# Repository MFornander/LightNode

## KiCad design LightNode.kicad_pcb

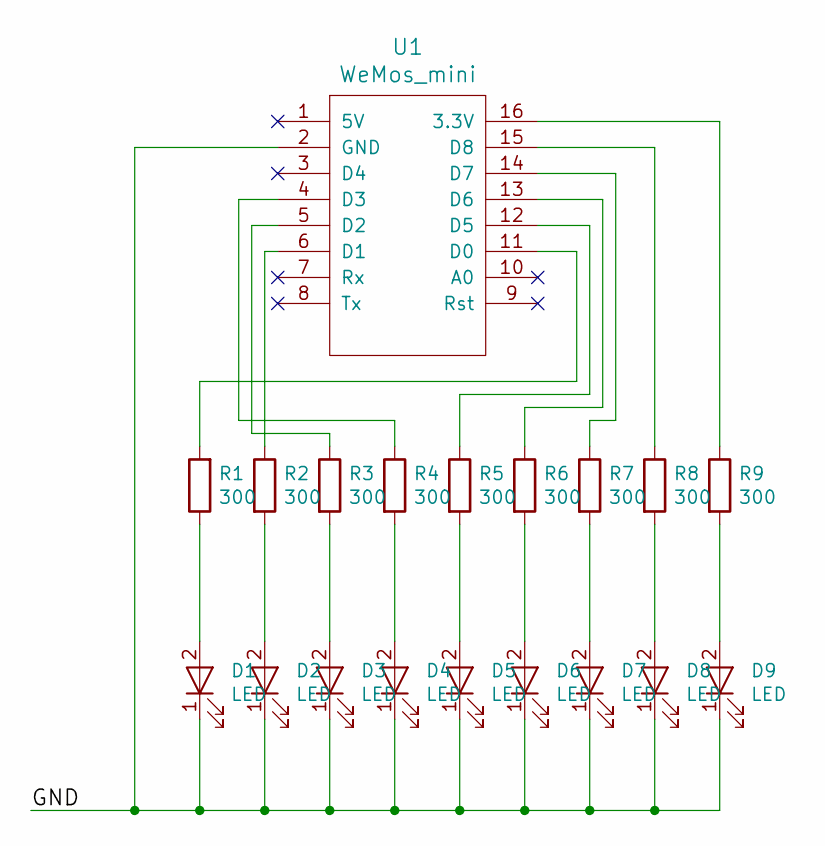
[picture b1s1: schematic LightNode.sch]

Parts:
D1, D2, D3, D4, D5, D6, D7, D8, D9: LED; LED_0805
R1, R2, R3, R4, R5, R6, R7, R8, R9: 300; R_0805
U1: WeMos_mini; D1_mini_board

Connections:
/GND: D1.1 (K), D2.1 (K), D3.1 (K), D4.1 (K), D5.1 (K), D6.1 (K), D7.1 (K), D8.1 (K), D9.1 (K), U1.2 (GND)
unnamed: D1.2 (A), R1.1
unnamed: D2.2 (A), R2.2
unnamed: D3.2 (A), R3.2
unnamed: D4.2 (A), R4.2
unnamed: D5.2 (A), R5.2
unnamed: D6.2 (A), R6.2
unnamed: D7.2 (A), R7.2
unnamed: D8.2 (A), R8.2
unnamed: D9.2 (A), R9.2
unnamed: R1.2, U1.11 (D0)
unnamed: R2.1, U1.6 (D1)
unnamed: R3.1, U1.5 (D2)
unnamed: R4.1, U1.4 (D3)
unnamed: R5.1, U1.12 (D5)
unnamed: R6.1, U1.13 (D6)
unnamed: R7.1, U1.14 (D7)
unnamed: R8.1, U1.15 (D8)
unnamed: R9.1, U1.16 (3.3V)

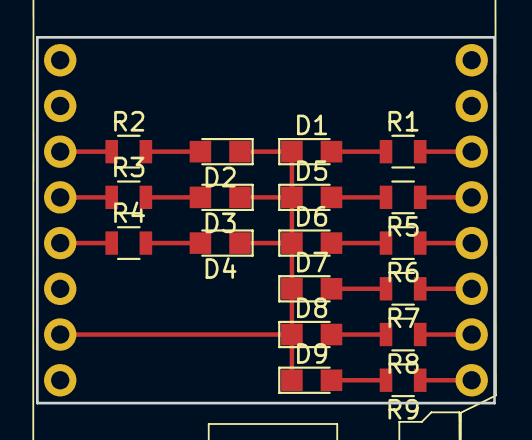
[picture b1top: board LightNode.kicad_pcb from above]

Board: 2 copper layers, 25.4 x 20.3 mm, 19 parts (0 on the bottom side), 19 nets.

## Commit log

2017-06-19 Initial PCB test of WEMOS GPIO LEDs
